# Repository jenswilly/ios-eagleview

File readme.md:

## EAGLEView app

**Now open source. Collaborators welcome.**

I have come to the conclusion that I simply do not have enough time to finish the EAGLEView app by myself. So I have decided to release the app as open source so everyone can download the source and build it.

Also, people are welcome (more than welcome, in fact) to contribute to the project.

The app is not finished but lots of functionality is already in place. These features already work:

- Display schematic and board files. EAGLE version 6 or higher.
- Open .sch or .brd file from Dropbox
- Open files by clicking links to .sch, .brd or .zip files (the zip file will be extracted and scanned for .sch and .brd files)
- Pan and zoom
- Click component to see details
- Search for specific components by name or value
- Show/hide individual layers
- Support for multiple modules

There is also some stuff that is not yet implemented. Among these are:

- Ploygon pours. (At the moment, the entire polygon will be filled completely.)
- Need to speed up drawing routines to avoid flickering when redrawing.
- Support for multiple sheets
- Different shapes for SMD pads
- Get the zoom-to-fit working properly
- And other stuff – refer to the `todo.txt` file

Remember, the app is read-only. You can't modify the schematics or boards. And it requires iOS 8.

### How to build

1. Get the code and open in the most recent Xcode.
2. Configure the project to use an appropriate bundle ID. You can either change the value directly in the `EAGLEView-Info.plist` file or you can change the value of the custom build setting named `BUNDLE_ID` (Project info -> Build Settings -> scroll down to the bottom).
3. Use the `Debug` or `Release` build scheme. The `Enterprise` is configured to use Crashlytics and the necessary bundle ID and API keys are external to the project so it will not work.
3. Run. You do need to be enrolled in Apple's iOS Developer Program in order to run the app on a device.

### How to contact me

Mail me at <jenswilly@gmail.com>.

### How to contribute

Just like any other GitHub project:

1. Fork the repository.
2. Make the fix.
3. Submit a pull request to me.

### More info

I will be posting updates on my website: <http://jenswilly.dk>.

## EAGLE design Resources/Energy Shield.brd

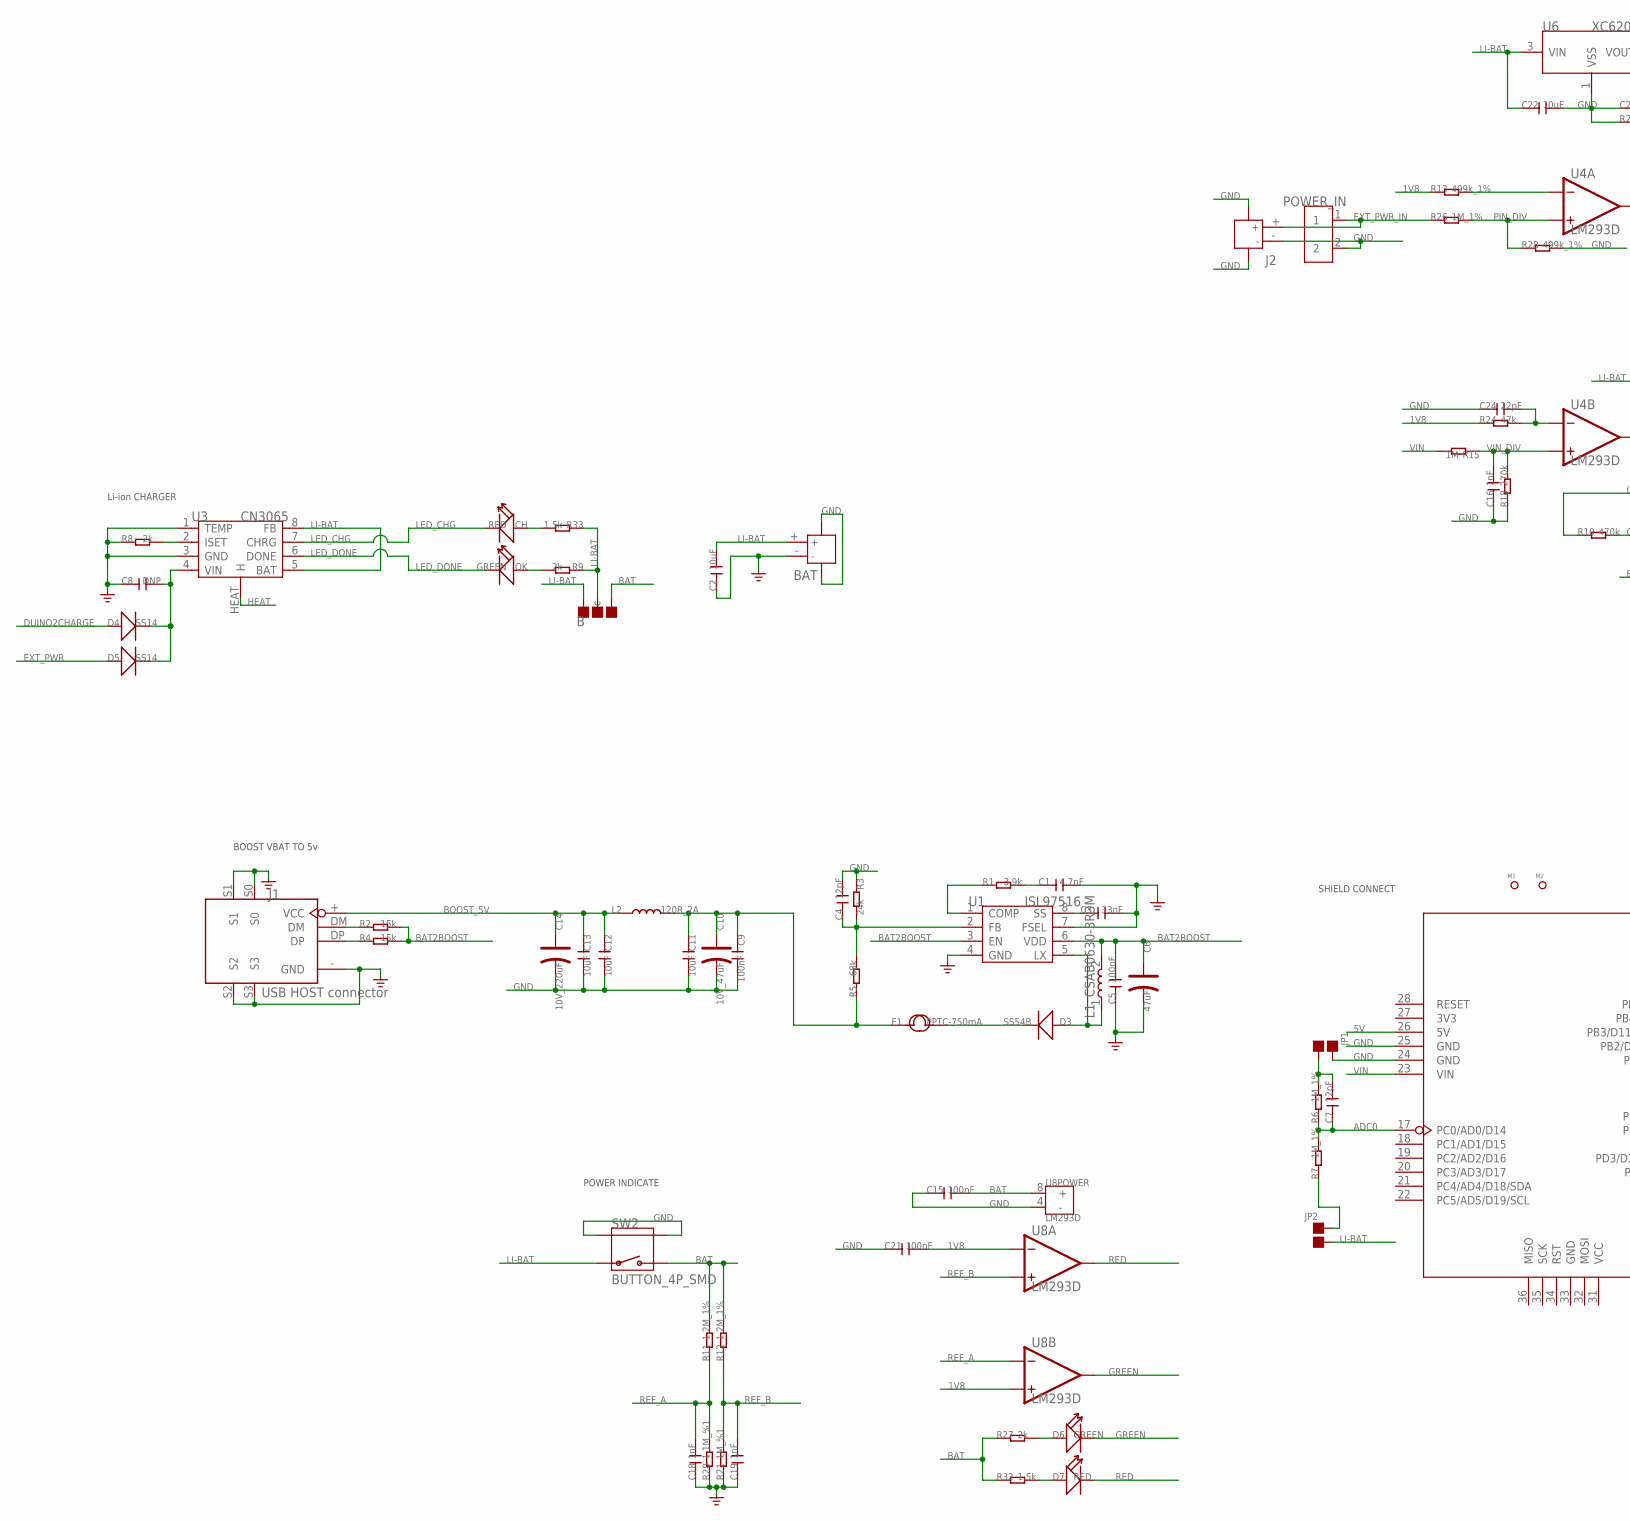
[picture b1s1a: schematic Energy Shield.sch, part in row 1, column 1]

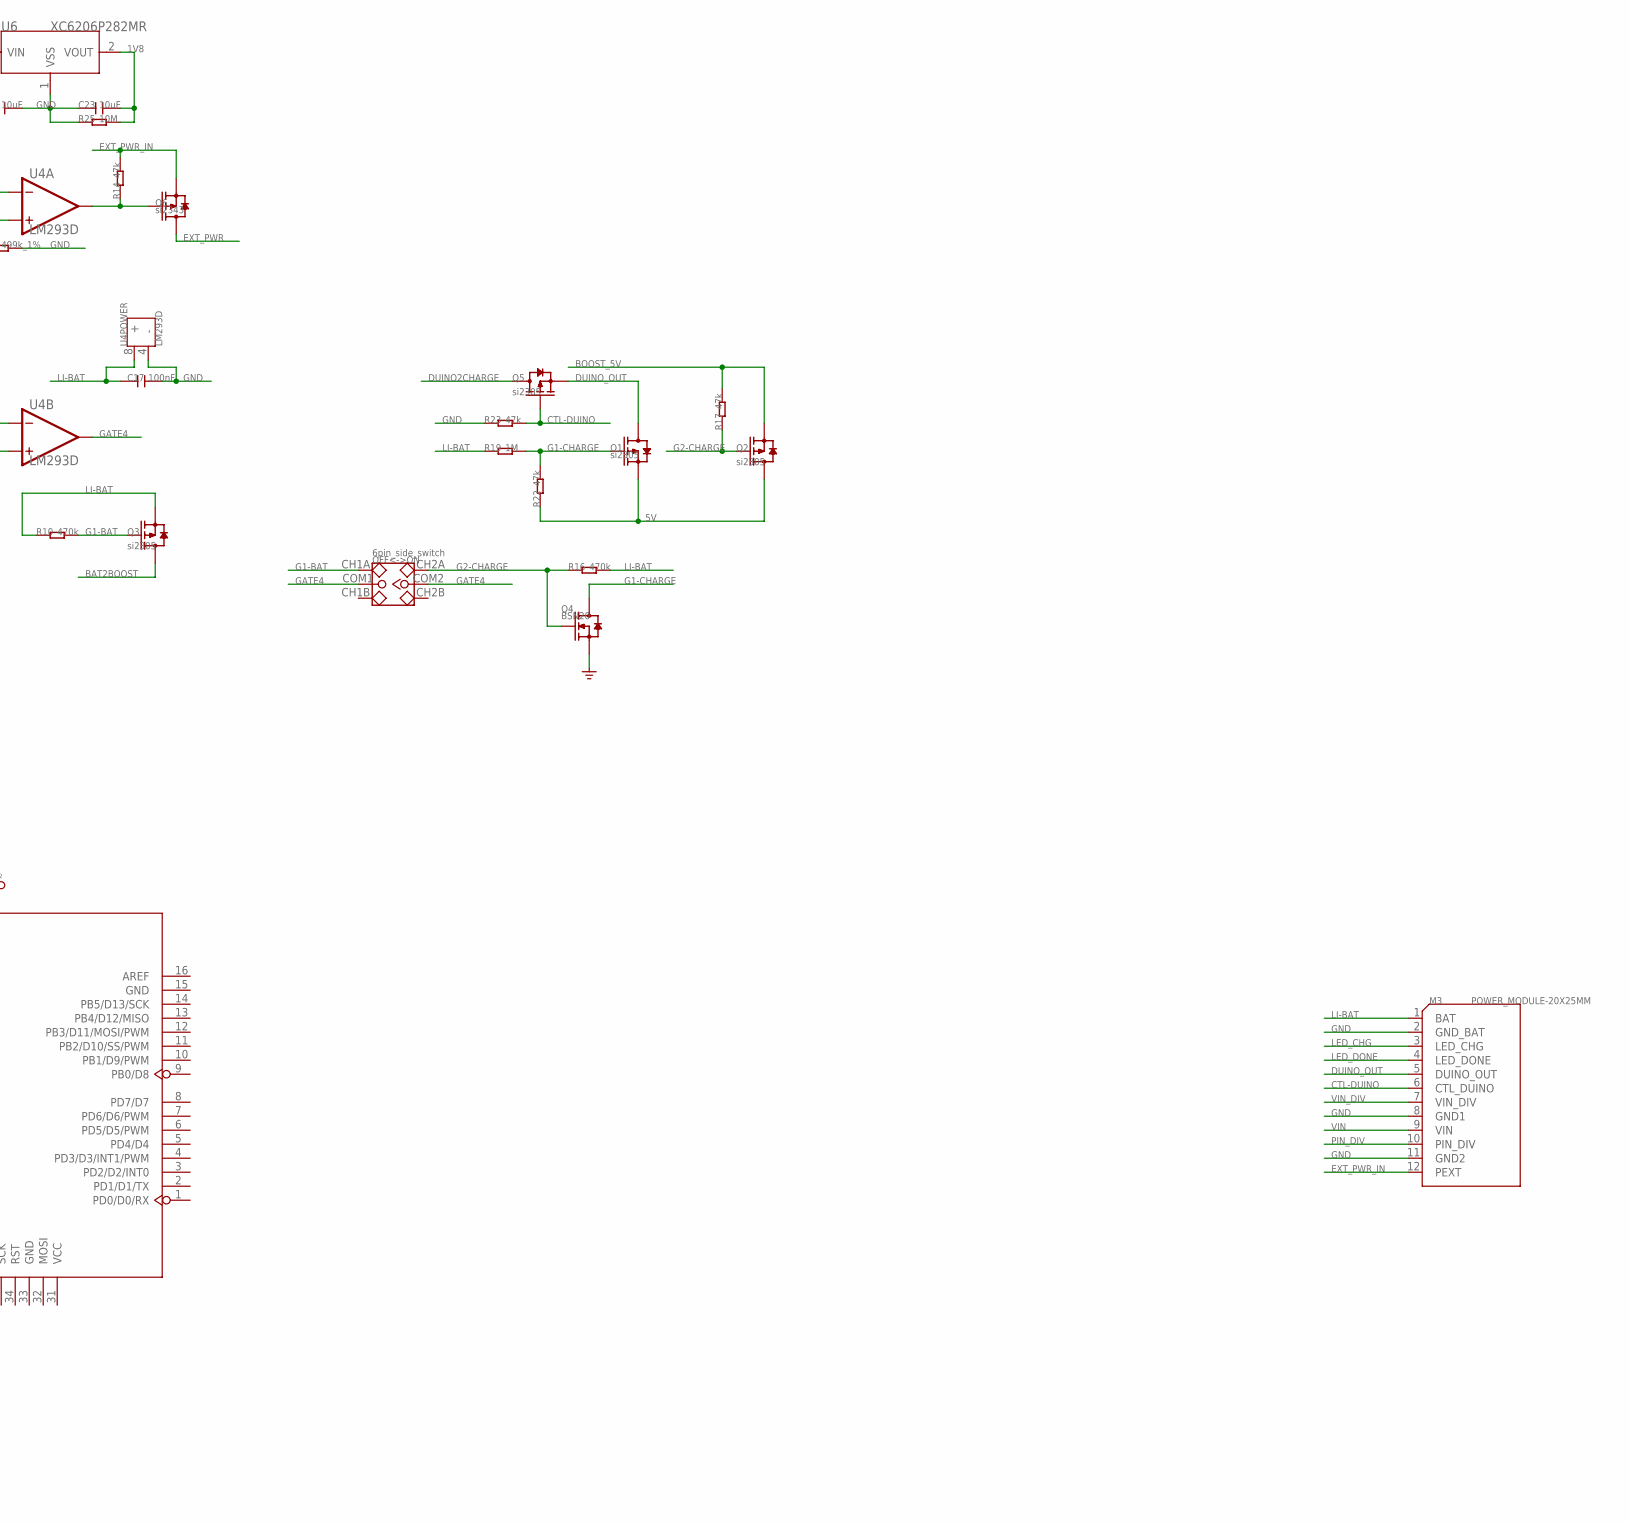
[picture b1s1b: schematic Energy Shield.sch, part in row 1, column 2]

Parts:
B: PAD-JUMPER-3P-40*40; 3P-SMD-4.1X1.5
BAT: JACK-JST-2P-SMD-PW'2.0'; JST-SMD-2.0-90D
C1: 4.7nF; C0603
C2, C11, C12, C13, C22, C23: 10uF; C0805
C3: 33nF; C0603
C4, C7: 12pF; C0603
C5, C9, C15, C17, C21: 100nF; C0603
C6: 47uF; AVX-B
C8: DNP; C0805
C10: 10V_47uF; AVX-B
C14: 10V_220uF; AVX-D
C16, C18, C19: 1nF; C0603
C24: 22pF; C0603
CH: RED; LED-SIDE-VIEW-0603-RIGHT
D3: SS54B; SMB
D4, D5: SS14; D2010
D6: GREEN; LED-SIDE-VIEW-0603-RIGHT
D7: RED; LED-SIDE-VIEW-0603-RIGHT
F1: PPTC-750mA; F1210
J1: USB HOST connector; FEMALE-14.5X13.2
J2: JACK-JST-2P-SMD-PW'2.0'; JST-SMD-2.0-90D
JP1: PAD-JUMPER-2P; 2P-SMD-1.78X1.27; PARTNO DNP
JP2: PAD-JUMPER-2P; 2P-SMD-1.78X1.27
L1: CSAB0630-3R3M; L0630
L2: 120R_2A; L0805
M1, M2: PAD-MARK; ROUND-MARK-1.0
M3: POWER_MODULE-20X25MM; POWER_MODULE
OFF<->ON: 6pin_side_switch; 6P-2CH-2.5-9.1X3.5X3.2H-90D
OK: GREEN; LED-SIDE-VIEW-0603-RIGHT
POWER_IN: SCREW-TERMINAL-2P'3.5'; 2P-3.5
Q1, Q2, Q3, Q5: si2305; SOT23
Q4: BSN20; SOT23
Q6: si2343; SOT23
R1: 3.9k; R0603
R2, R4: 15k; R0603
R3: 24k; R0603
R5: 68k; R0603
R6, R7, R26: 1M_1%; R0603
R8, R9, R27: 2k; R0603
R10, R16: 470k; R0603
R11, R12: 1.2M_1%; R0603
R13, R28: 499k_1%; R0603
R14, R17, R22, R23, R24: 47k; R0603
R15, R19: 1M; R0603
R18: 270k; R0603
R20: 1.1M_%1; R0603
R21: 1M_%1; R0603
R25: 10M; R0603
R32, R33: 1.5k; R0603
SW2: BUTTON_4P_SMD; 4P-SMD-7X3.5X3.5
U1: ISL97516; MSOP8
U2: ARDUINO'W/O-SILK'; ARDUINO-W/O-SILK
U3: CN3065; DFN8
U4, U8: LM293D; SOIC8-6.0
U6: XC6206P282MR; SOT23

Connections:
1V8: C21.2, C23.2, R13.1, R24.1, R25.2, U6.2 (VOUT), U8.2 (IN-), U8.5 (IN+)
5V: Q1.2 (S), Q2.3 (D), R22.1, U2.26 (5V)
ADC0: C7.1, R6.1, R7.2, U2.17 (PC0/AD0/D14)
BAT: B.00 (L), C15.2, R11.2, R12.2, R27.1, R32.1, SW2.2, U8.8 (+)
BAT2BOOST: C5.2, C6.+, L1.2, Q3.3 (D), R2.2, R4.2, U1.3 (EN), U1.6 (VDD)
BOOST_5V: C12.1, C13.1, C14.+, J1.+ (VCC), L2.1, Q2.2 (S), R17.2
CTL-DUINO: M3.6 (CTL_DUINO), Q5.1 (G), R23.2
DUINO2CHARGE: D4.+, Q5.3 (D)
DUINO_OUT: M3.5 (DUINO_OUT), Q1.3 (D), Q5.2 (S)
EXT_PWR: D5.+, Q6.3 (D)
EXT_PWR_IN: J2.+ (1), M3.12 (PEXT), POWER_IN.1, Q6.2 (S), R14.2, R26.1
G1-BAT: OFF<->ON.CH1A, Q3.1 (G), R10.2
G1-CHARGE: Q1.1 (G), Q4.3 (D), R19.2, R22.2
G2-CHARGE: OFF<->ON.CH2A, Q2.1 (G), Q4.1 (G), R16.1, R17.1
GATE4: OFF<->ON.COM1, OFF<->ON.COM2, U4.7 (OUT)
GND: BAT.3, BAT.4, BAT.- (2), C1.2, C2.1, C3.2, C4.2, C5.1, C6.-, C8.1, C9.2, C10.-, C11.2, C12.2, C13.2, C14.-, C15.1, C16.1, C17.1, C18.1, C19.1, C21.1, C22.2, C23.1, C24.1, J1.- (GND), J1.S0, J1.S1, J1.S2, J1.S3, J2.3, J2.4, J2.- (2), JP1.2, M3.2 (GND_BAT), M3.8 (GND1), M3.11 (GND2), POWER_IN.2, Q4.2 (S), R3.1, R8.1, R18.1, R20.1, R21.1, R23.1, R25.1, R28.2, SW2.S1, SW2.S2, U1.4 (GND), U1.7 (FSEL), U2.24 (GND), U2.25 (GND), U3.1 (TEMP), U3.3 (GND), U4.4 (-), U6.1 (VSS), U8.4 (-)
GREEN: D6.2 (-), U8.7 (OUT)
HEAT: U3.HEAT (H)
LED_CHG: CH.2 (-), M3.3 (LED_CHG), U3.7 (CHRG)
LED_DONE: M3.4 (LED_DONE), OK.2 (-), U3.6 (DONE)
LI-BAT: B.11 (R), B.MM (C), BAT.+ (1), C2.2, C17.2, C22.1, JP2.1, M3.1 (BAT), Q3.2 (S), R9.1, R10.1, R16.2, R19.1, R33.1, SW2.1, U3.5 (BAT), U3.8 (FB), U4.8 (+), U6.3 (VIN)
unnamed: R1.1, U1.1 (COMP)
unnamed: C1.1, R1.2
unnamed: C4.1, R3.2, R5.2, U1.2 (FB)
unnamed: D3.+, L1.1, U1.5 (LX)
unnamed: C9.1, C10.+, C11.1, F1.1, L2.2, R5.1
unnamed: C3.1, U1.8 (SS)
unnamed: R8.2, U3.2 (ISET)
unnamed: Q6.1 (G), R14.1, U4.1 (OUT)
unnamed: D6.1 (+), R27.2
unnamed: OK.1 (+), R9.2
unnamed: D7.1 (+), R32.2
unnamed: R13.2, U4.2 (IN-)
unnamed: CH.1 (+), R33.2
unnamed: J1.DM, R2.1
unnamed: J1.DP, R4.1
unnamed: D3.-, F1.2
unnamed: JP2.2, R7.1
unnamed: C7.2, JP1.1, R6.2
P$1: C24.2, R24.2, U4.6 (IN-)
PIN_DIV: M3.10 (PIN_DIV), R26.2, R28.1, U4.3 (IN+)
RED: D7.2 (-), U8.1 (OUT)
REF_A: C18.2, R11.1, R20.2, U8.6 (IN-)
REF_B: C19.2, R12.1, R21.2, U8.3 (IN+)
VCHG_IN: C8.2, D4.-, D5.-, U3.4 (VIN)
VIN: M3.9 (VIN), R15.2, U2.23 (VIN)
VIN_DIV: C16.2, M3.7 (VIN_DIV), R15.1, R18.2, U4.5 (IN+)

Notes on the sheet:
SHIELD CONNECT
Li-ion CHARGER
BOOST VBAT TO 5v
POWER INDICATE

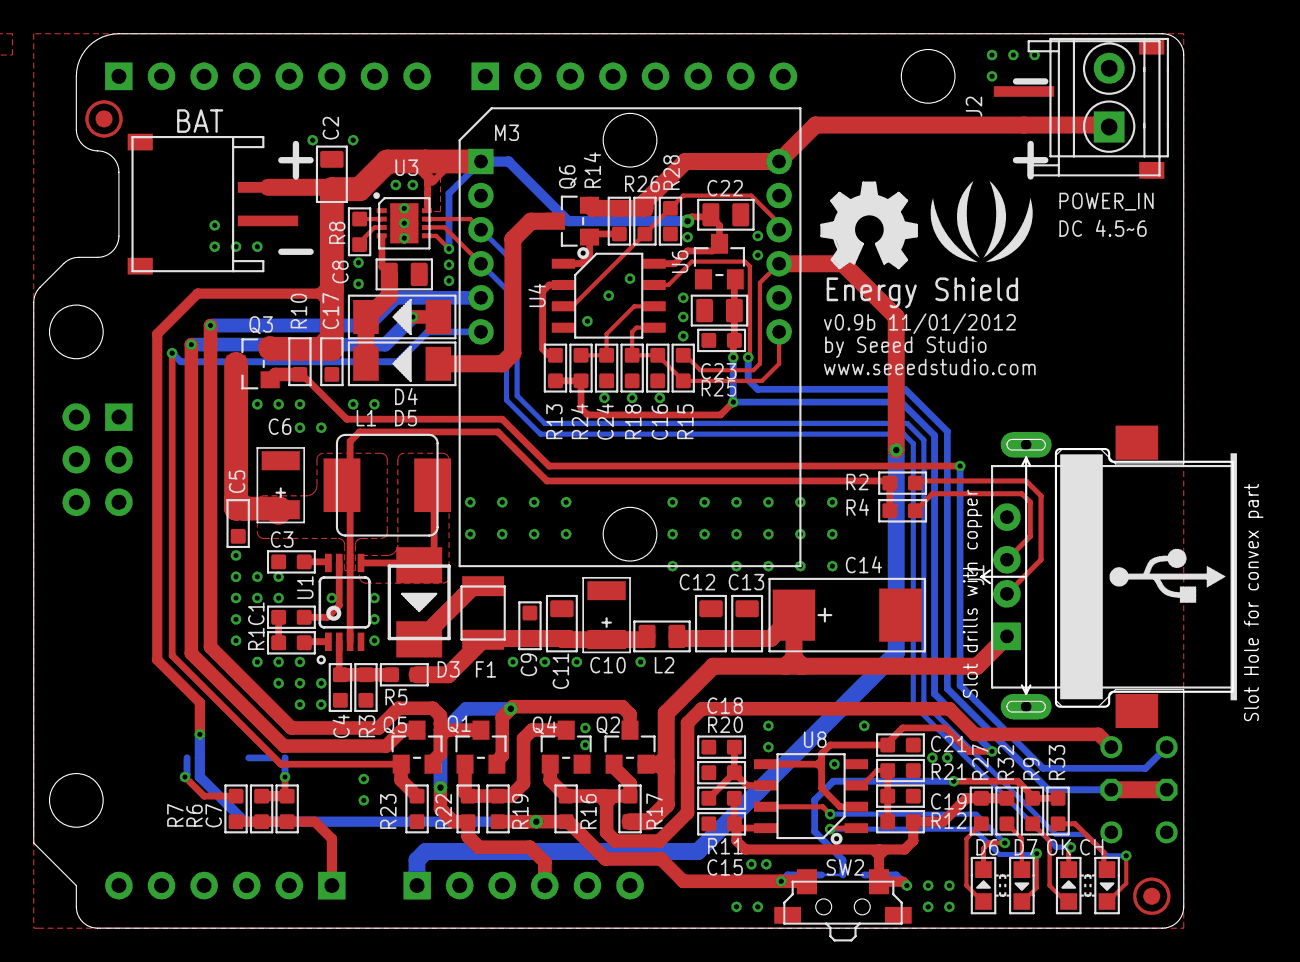
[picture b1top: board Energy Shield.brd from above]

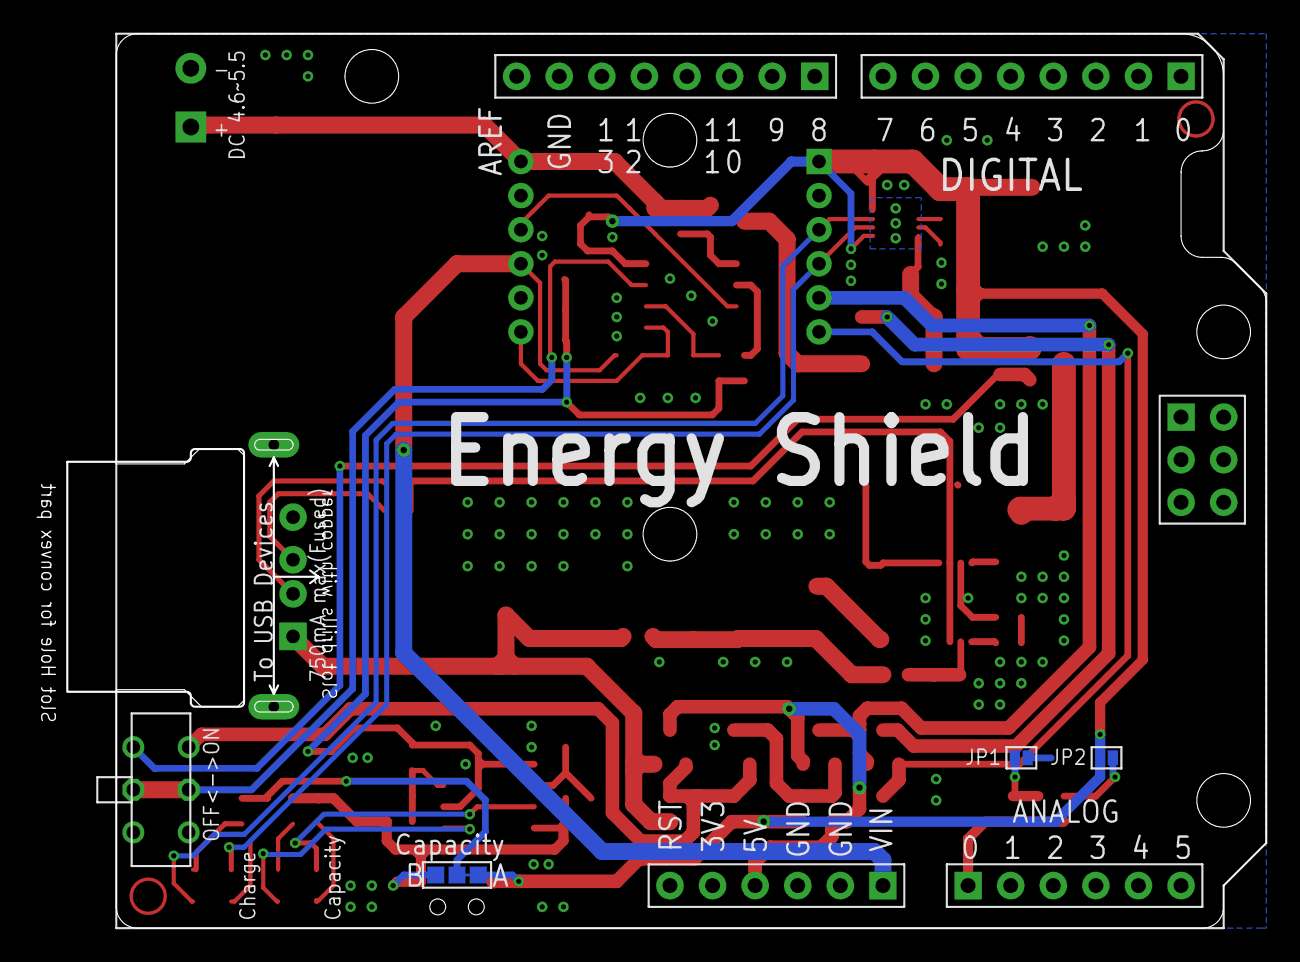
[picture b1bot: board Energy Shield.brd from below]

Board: 2 copper layers, 73.4 x 53.2 mm, 89 parts (5 on the bottom side), 46 nets.

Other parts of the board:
U$17: OSHW_FILLX200_NOTEXT
U$18: LOGO_SILK

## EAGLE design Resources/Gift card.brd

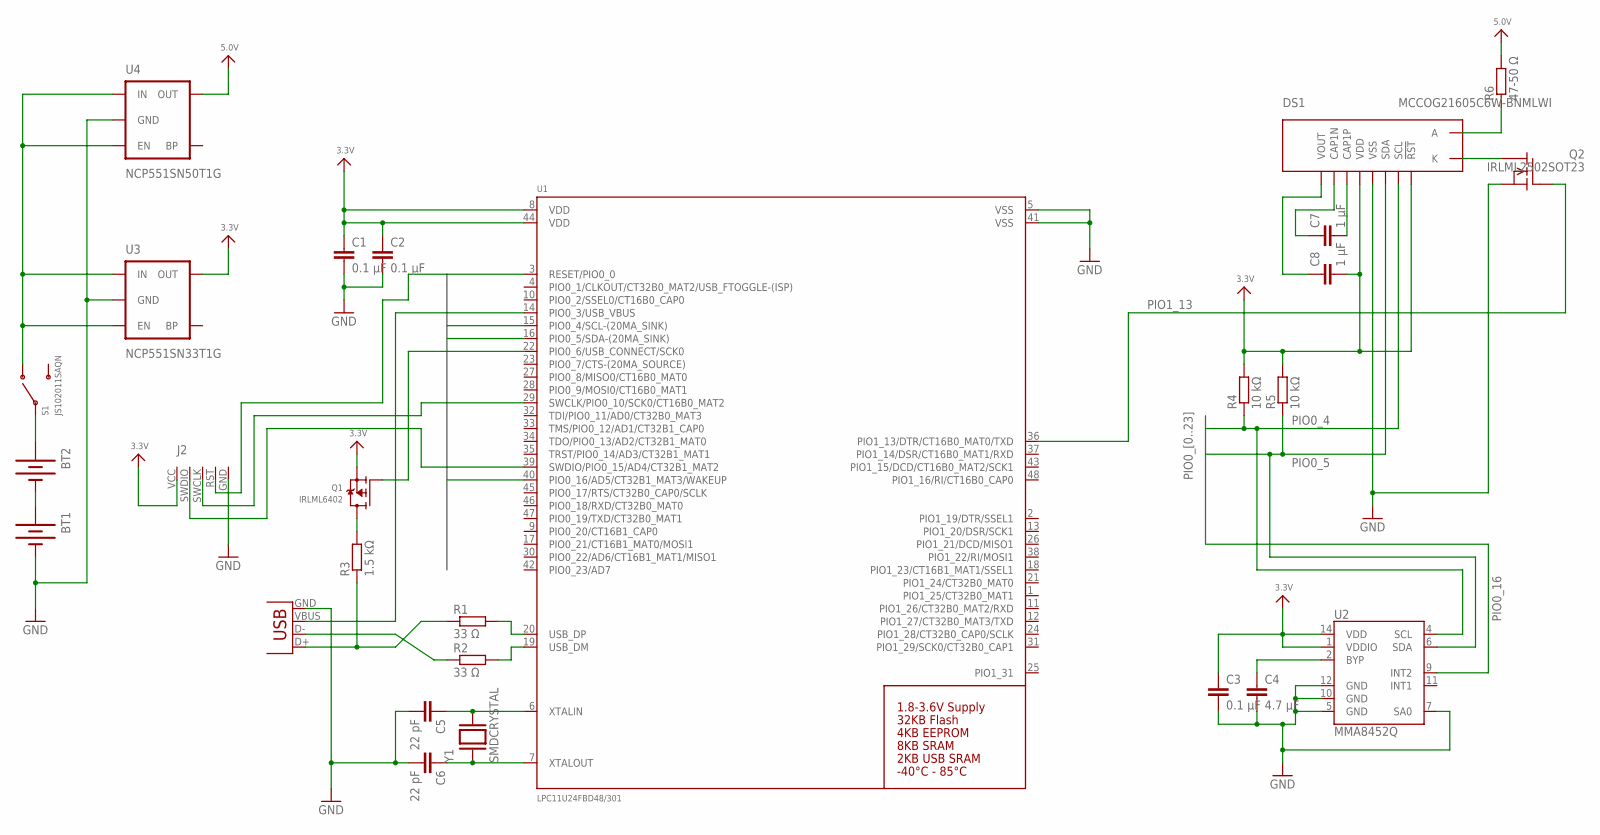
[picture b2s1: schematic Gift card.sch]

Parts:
BT1, BT2: BATTERY20SMD; BATTCON_20MM
C1, C2, C3: 0.1 µF; C0805
C4: 4.7 µF; C0805
C5, C6: 22 pF; C0805
C7, C8: 1 µF; C0805
DS1: MCCOG21605C6W-BNMLWI
J1: USBSMD; USB-MINIB
J2: LPC_SWD_PINPROG; LPC_SWD_PINS
Q1: IRLML6402; SOT23-WIDE
Q2: IRLML2502SOT23; SOT23-3
R1, R2: 33 Ω; R0805
R3: 1.5 kΩ; R0805
R4, R5: 10 kΩ; R0805
R6: 47-50 Ω; R0805
S1: JS102011SAQN
U1: LPC11U24FBD48/301; LQFP48
U2: MMA8452Q; QFN-16_0.5MM
U3: NCP551SN33T1G; SOT23-5
U4: NCP551SN50T1G; SOT23-5
Y1: SMDCRYSTAL; XTAL_ABM7

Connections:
3V3: C1.1, C2.1, C3.1, C8.2, DS1.P$4 (VDD), DS1.P$8 (!RST), J2.VCC, Q1.2 (S), R4.2, R5.2, U1.8 (VDD), U1.44 (VDD), U2.1 (VDDIO), U2.14 (VDD), U3.5 (OUT)
5V: R6.2, U4.5 (OUT)
GND: BT1.2 (-), C1.2, C2.2, C3.2, C4.2, C5.2, C6.2, DS1.P$5 (VSS), J1.GND, J2.GND, Q2.2 (S), U1.5 (VSS), U1.41 (VSS), U2.5 (GND), U2.7 (SA0), U2.10 (GND), U2.12 (GND), U3.2 (GND), U4.2 (GND)
unnamed: BT1.1 (+), BT1.3 (+), BT2.2 (-)
unnamed: J1.D+, R1.1, R3.1
unnamed: R1.2, U1.20 (USB_DP)
unnamed: R2.2, U1.19 (USB_DM)
unnamed: J1.D-, R2.1
unnamed: Q1.3 (D), R3.2
unnamed: C5.1, U1.6 (XTALIN), Y1.P$2 (2)
unnamed: C6.1, U1.7 (XTALOUT), Y1.P$1 (1)
unnamed: DS1.K, Q2.3 (D)
unnamed: BT2.1 (+), BT2.3 (+), S1.P$2 (2)
unnamed: C7.1, DS1.P$2 (CAP1N)
unnamed: C7.2, DS1.P$3 (CAP1P)
unnamed: C8.1, DS1.P$1 (VOUT)
unnamed: C4.1, U2.2 (BYP)
PIO0_0: J2.RST (!RST), U1.3 (RESET/PIO0_0)
PIO0_3: J1.VBUS, U1.14 (PIO0_3/USB_VBUS)
PIO0_4: DS1.P$7 (SCL), R4.1, U1.15 (PIO0_4/SCL-(20MA_SINK)), U2.4 (SCL)
PIO0_5: DS1.P$6 (SDA), R5.1, U1.16 (PIO0_5/SDA-(20MA_SINK)), U2.6 (SDA)
PIO0_6: Q1.1 (G), U1.22 (PIO0_6/USB_CONNECT/SCK0)
PIO0_10: J2.SWCLK, U1.29 (SWCLK/PIO0_10/SCK0/CT16B0_MAT2)
PIO0_15: J2.SWDIO (SWD), U1.39 (SWDIO/PIO0_15/AD4/CT32B1_MAT2)
PIO0_16: U1.40 (PIO0_16/AD5/CT32B1_MAT3/WAKEUP), U2.9 (INT2)
PIO1_13: Q2.1 (G), U1.36 (PIO1_13/DTR/CT16B0_MAT0/TXD)
VIN: S1.P$1 (1), U3.1 (IN), U3.3 (EN), U4.1 (IN), U4.3 (EN)
VLED: DS1.A, R6.1

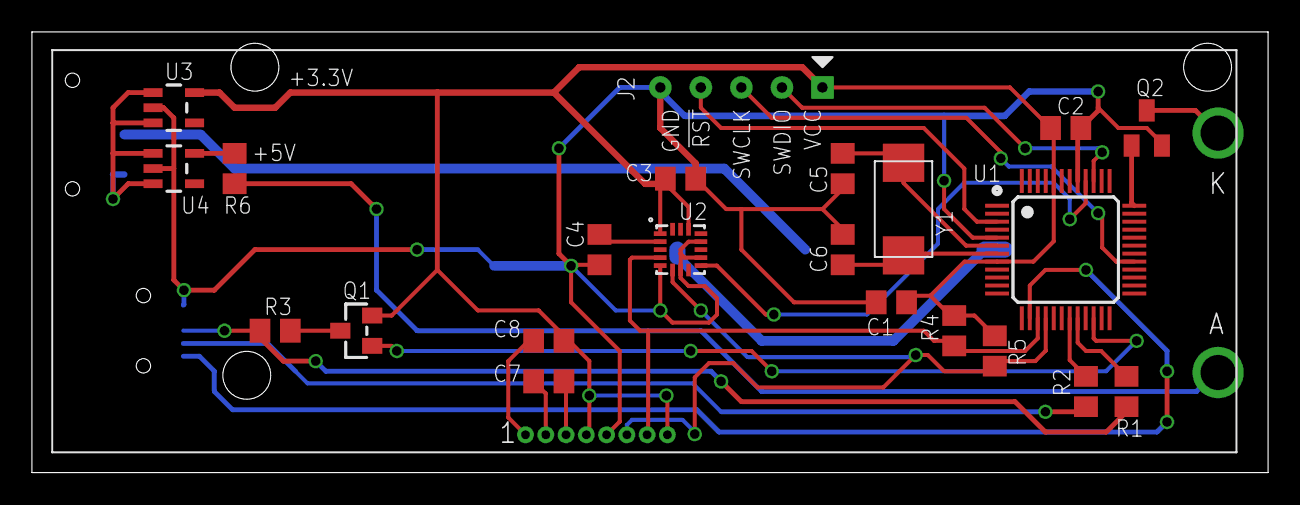
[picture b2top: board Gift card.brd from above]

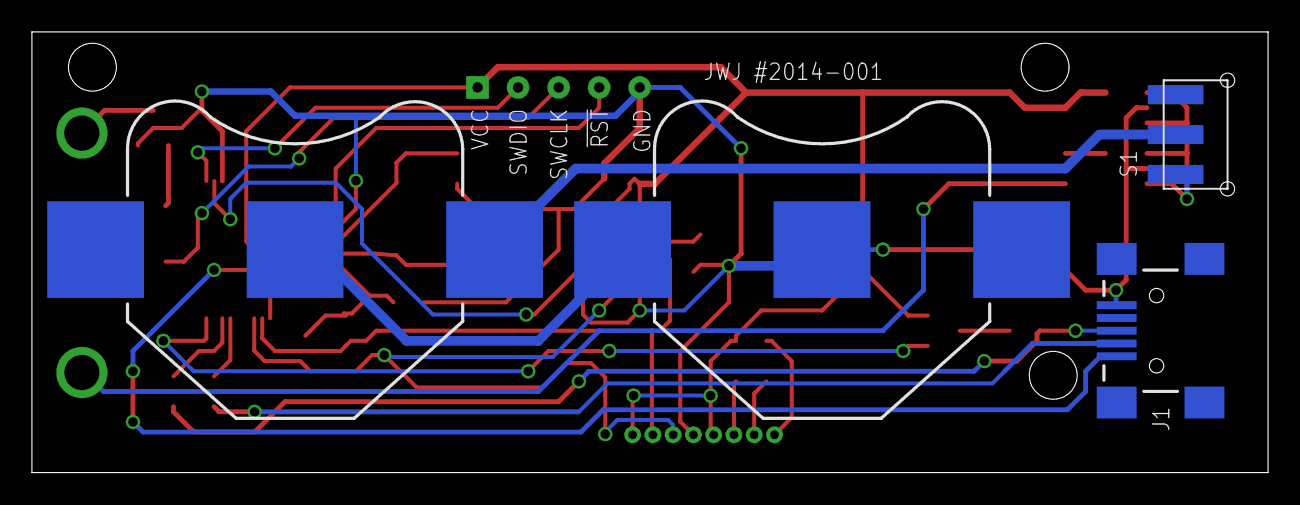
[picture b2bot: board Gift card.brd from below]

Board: 2 copper layers, 77.5 x 27.6 mm, 27 parts (4 on the bottom side), 28 nets.

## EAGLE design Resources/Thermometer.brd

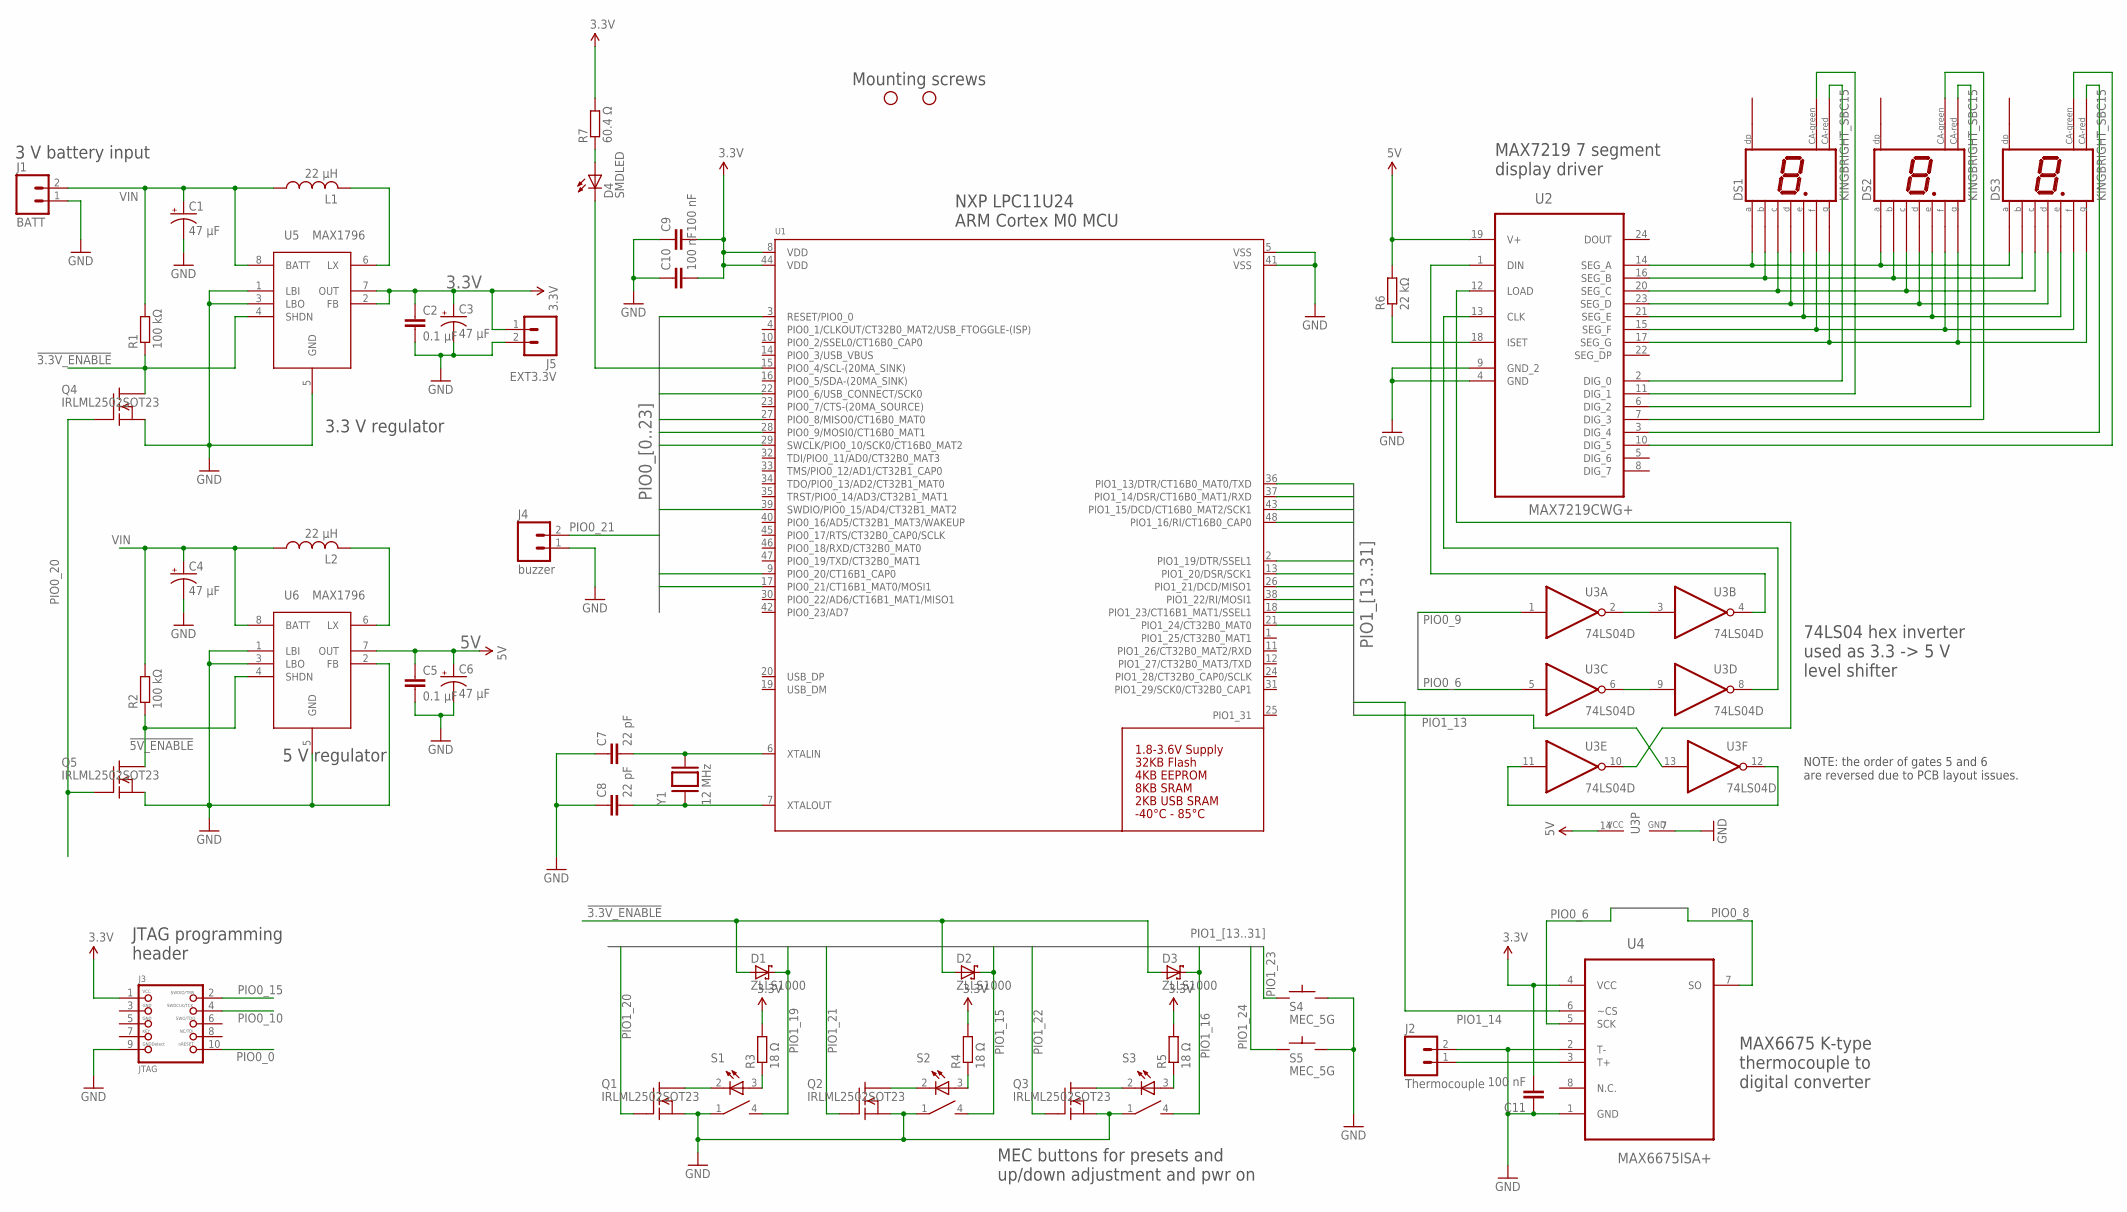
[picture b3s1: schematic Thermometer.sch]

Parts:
C1, C3, C4, C6: 47 µF; SMC_B
C2, C5: 0.1 µF; C0805K
C7, C8: 22 pF; C0805K
C9, C10, C11: 100 nF; C0805K
D1, D2, D3: ZLLS1000; SOT23
D4: SMDLED; 1206
DS1, DS2, DS3: KINGBRIGHT_SBC15; 7-SEG_SBC15
J1: BATT; 1X02
J2: Thermocouple; 1X02_LONGPADS
J3: JTAG; 2X05_1.27MM_SMT
J4: buzzer; 1X02
J5: EXT3.3V; 1X02
L1, L2: 22 µH; ELL5PS_INDUCTOR
MP1, MP2: STAND-OFF
Q1, Q2, Q3, Q4, Q5: IRLML2502SOT23; SOT23-3
R1, R2: 100 kΩ; M0805
R3, R4, R5: 18 Ω; M0805
R6: 22 kΩ; M0805
R7: 60.4 Ω; M0805
S1, S2, S3: ILLUMEC-4FTH9; ILLUMEC-4F-TH9; FARNELL 2280492
S4, S5: MEC_5G; ILLUMEC-4F-TH9; FARNELL 2280480
U1: LPC11U24_QFP48; LQFP48
U2: MAX7219CWG+; SOIC127P1032X265-24N
U3: 74LS04D; SO14
U4: MAX6675ISA+; SOIC127P600X175-8N
U5, U6: MAX1796; UMAX8
Y1: 12 MHz; XTAL_ABM7

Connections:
3.3V: C2.1, C3.+, C9.2, C10.2, C11.2, J3.1, J5.1, R3.2, R4.2, R5.2, R7.2, U1.8 (VDD), U1.44 (VDD), U4.4 (VCC), U5.2 (FB), U5.7 (OUT)
5V: C5.1, C6.+, R6.2, U2.19 (V+), U3.14 (VCC), U6.7 (OUT)
!3.3V_ENABLE: D1.1 (A), D2.1 (A), D3.1 (A), Q4.3 (D), R1.1, U5.4 (SHDN)
!5V_ENABLE: Q5.3 (D), R2.1, U6.4 (SHDN)
GND: C1.-, C2.2, C3.-, C4.-, C5.2, C6.-, C7.1, C8.1, C9.1, C10.1, C11.1, J1.1, J2.2, J3.9, J4.1, J5.2, Q1.2 (S), Q2.2 (S), Q3.2 (S), Q4.2 (S), Q5.2 (S), S1.1, S2.1, S3.1, S4.3, S4.4, S5.3, S5.4, U1.5 (VSS), U1.41 (VSS), U2.4 (GND), U2.9 (GND_2), U3.7 (GND), U4.1 (GND), U4.2 (T-), U5.1 (LBI), U5.3 (LBO), U5.5 (GND), U6.1 (LBI), U6.2 (FB), U6.3 (LBO), U6.5 (GND)
unnamed: DS1.P$7 (A), DS2.P$7 (A), DS3.P$7 (A), U2.14 (SEG_A)
unnamed: DS1.P$6 (B), DS2.P$6 (B), DS3.P$6 (B), U2.16 (SEG_B)
unnamed: DS1.P$4 (C), DS2.P$4 (C), DS3.P$4 (C), U2.20 (SEG_C)
unnamed: DS1.P$3 (D), DS2.P$3 (D), DS3.P$3 (D), U2.23 (SEG_D)
unnamed: DS1.P$2 (E), DS2.P$2 (E), DS3.P$2 (E), U2.21 (SEG_E)
unnamed: DS1.P$9 (F), DS2.P$9 (F), DS3.P$9 (F), U2.15 (SEG_F)
unnamed: DS1.P$10 (G), DS2.P$10 (G), DS3.P$10 (G), U2.17 (SEG_G)
unnamed: DS2.P$5 (CA-G), U2.7 (DIG_3)
unnamed: DS2.P$1 (CA-R), U2.6 (DIG_2)
unnamed: DS3.P$1 (CA-R), U2.3 (DIG_4)
unnamed: DS1.P$5 (CA-G), U2.11 (DIG_1)
unnamed: DS1.P$1 (CA-R), U2.2 (DIG_0)
unnamed: DS3.P$5 (CA-G), U2.10 (DIG_5)
unnamed: R5.1, S3.3 (A)
unnamed: U3.2 (O), U3.3 (I)
unnamed: U2.1 (DIN), U3.4 (O)
unnamed: U2.13 (CLK), U3.8 (O)
unnamed: U2.12 (LOAD), U3.10 (O)
unnamed: R6.1, U2.18 (ISET)
unnamed: Q3.3 (D), S3.2 (C)
unnamed: R4.1, S2.3 (A)
unnamed: R3.1, S1.3 (A)
unnamed: Q2.3 (D), S2.2 (C)
unnamed: Q1.3 (D), S1.2 (C)
unnamed: J2.1, U4.3 (T+)
unnamed: C7.2, U1.6 (XTALIN), Y1.P$2 (2)
unnamed: C8.2, U1.7 (XTALOUT), Y1.P$1 (1)
unnamed: D4.1 (A), R7.1
unnamed: L2.P$2 (2), U6.6 (LX)
unnamed: U3.6 (O), U3.9 (I)
unnamed: L1.P$2 (2), U5.6 (LX)
unnamed: U3.11 (I), U3.12 (O)
PIO0_0: J3.10, U1.3 (RESET/PIO0_0)
PIO0_4: D4.2 (C), U1.15 (PIO0_4/SCL-(20MA_SINK))
PIO0_6: U1.22 (PIO0_6/USB_CONNECT/SCK0), U3.5 (I), U4.5 (SCK)
PIO0_8: U1.27 (PIO0_8/MISO0/CT16B0_MAT0), U4.7 (SO)
PIO0_9: U1.28 (PIO0_9/MOSI0/CT16B0_MAT1), U3.1 (I)
PIO0_10: J3.4, U1.29 (SWCLK/PIO0_10/SCK0/CT16B0_MAT2)
PIO0_15: J3.2, U1.39 (SWDIO/PIO0_15/AD4/CT32B1_MAT2)
PIO0_20: Q4.1 (G), Q5.1 (G), U1.9 (PIO0_20/CT16B1_CAP0)
PIO0_21: J4.2, U1.17 (PIO0_21/CT16B1_MAT0/MOSI1)
PIO1_13: U1.36 (PIO1_13/DTR/CT16B0_MAT0/TXD), U3.13 (I)
PIO1_14: U1.37 (PIO1_14/DSR/CT16B0_MAT1/RXD), U4.6 (~CS)
PIO1_15: D2.3 (C), S2.4, U1.43 (PIO1_15/DCD/CT16B0_MAT2/SCK1)
PIO1_16: D3.3 (C), S3.4, U1.48 (PIO1_16/RI/CT16B0_CAP0)
PIO1_19: D1.3 (C), S1.4, U1.2 (PIO1_19/DTR/SSEL1)
PIO1_20: Q1.1 (G), U1.13 (PIO1_20/DSR/SCK1)
PIO1_21: Q2.1 (G), U1.26 (PIO1_21/DCD/MISO1)
PIO1_22: Q3.1 (G), U1.38 (PIO1_22/RI/MOSI1)
PIO1_23: S4.1, S4.2, U1.18 (PIO1_23/CT16B1_MAT1/SSEL1)
PIO1_24: S5.1, S5.2, U1.21 (PIO1_24/CT32B0_MAT0)
VIN: C1.+, C4.+, J1.2, L1.P$1 (1), L2.P$1 (1), R1.2, R2.2, U5.8 (BATT), U6.8 (BATT)

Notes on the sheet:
3.3 V regulator
5 V regulator
NOTE: the order of gates 5 and 6 are reversed due to PCB layout issues.
Mounting screws
74LS04 hex inverter used as 3.3 -> 5 V level shifter
MAX7219 7 segment display driver
MAX6675 K-type thermocouple to digital converter
NXP LPC11U24 ARM Cortex M0 MCU
MEC buttons for presets and up/down adjustment and pwr on
JTAG programming header
3 V battery input

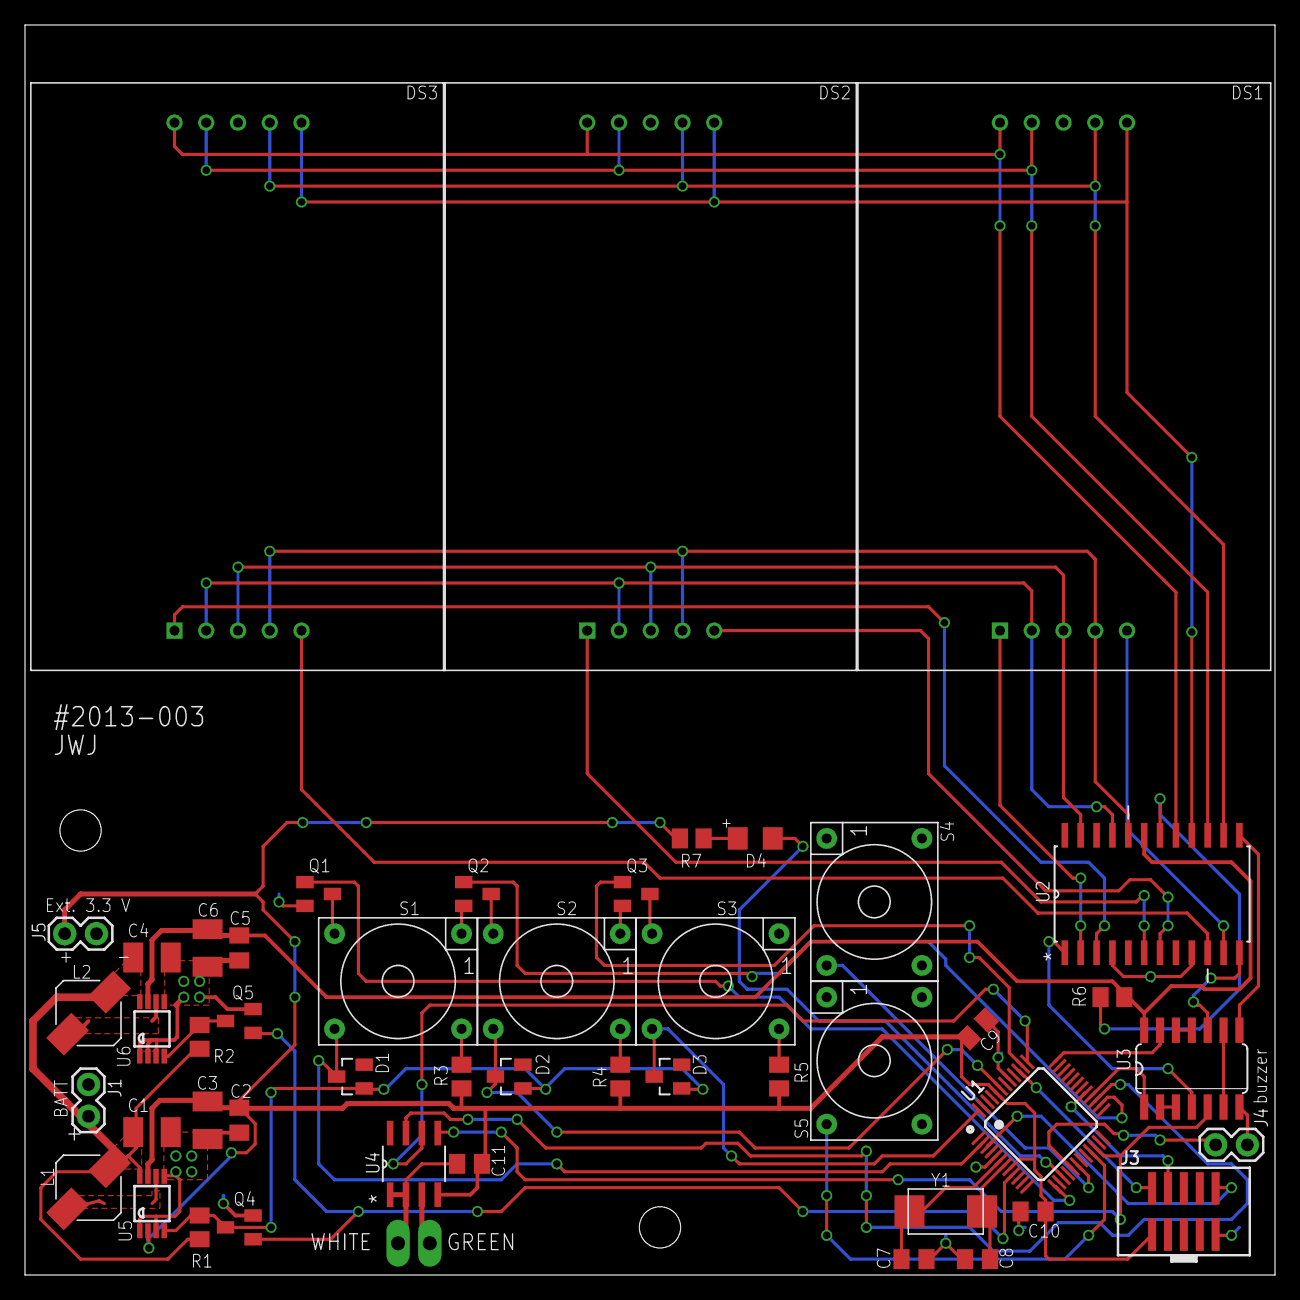
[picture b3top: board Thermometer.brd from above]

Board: 2 copper layers, 100.0 x 100.0 mm, 51 parts (0 on the bottom side), 57 nets.

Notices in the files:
parts and their libraries:
microbuilder: This work is placed in the public domain, and may be freely used for commercial and non-commercial work with the following conditions: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
SparkFun-Connectors: Licensing: CC v3.0 Share-Alike You are welcome to use this library for commercial purposes.
